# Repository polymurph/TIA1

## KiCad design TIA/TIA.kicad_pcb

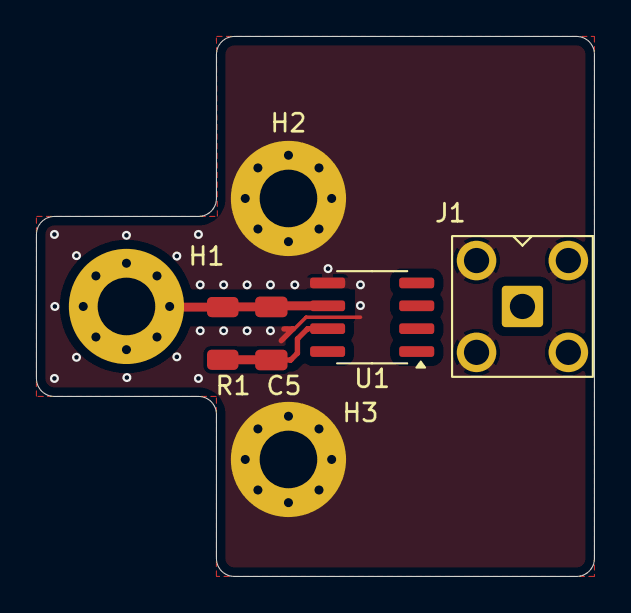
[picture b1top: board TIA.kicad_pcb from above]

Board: 2 copper layers, 31.0 x 30.0 mm, 7 parts (0 on the bottom side), 3 nets.

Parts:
C5: 160p; C_1206_3216Metric
H1, H2, H3: MountingHole_Pad; MountingHole_3.2mm_M3_Pad_Via
J1: Conn_Coaxial; SMA_BAT_Wireless_BWSMA-KWE-Z001
R1: 1M; R_1206_3216Metric
U1: AD8552ARZ; SOIC-8_3.9x4.9mm_P1.27mm

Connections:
/IN: C5.1, H1.1, R1.1, U1.6 (-)
GND: H2.1, H3.1, J1.2 (Ext), U1.5 (+)
unnamed: C5.2, R1.2, U1.7

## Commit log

2025-01-24 added Readme.md
2025-01-24 added .gitignore
2025-01-25 srarted work
2025-01-26 added LT spice to .gitignore
2025-01-26 added .lck files to .gitignore
